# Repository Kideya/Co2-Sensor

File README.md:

Ich bin ein Pferd und weiß nicht wie man ein Readme schreibt. Man mag es mir verzeihen.
Cheers.

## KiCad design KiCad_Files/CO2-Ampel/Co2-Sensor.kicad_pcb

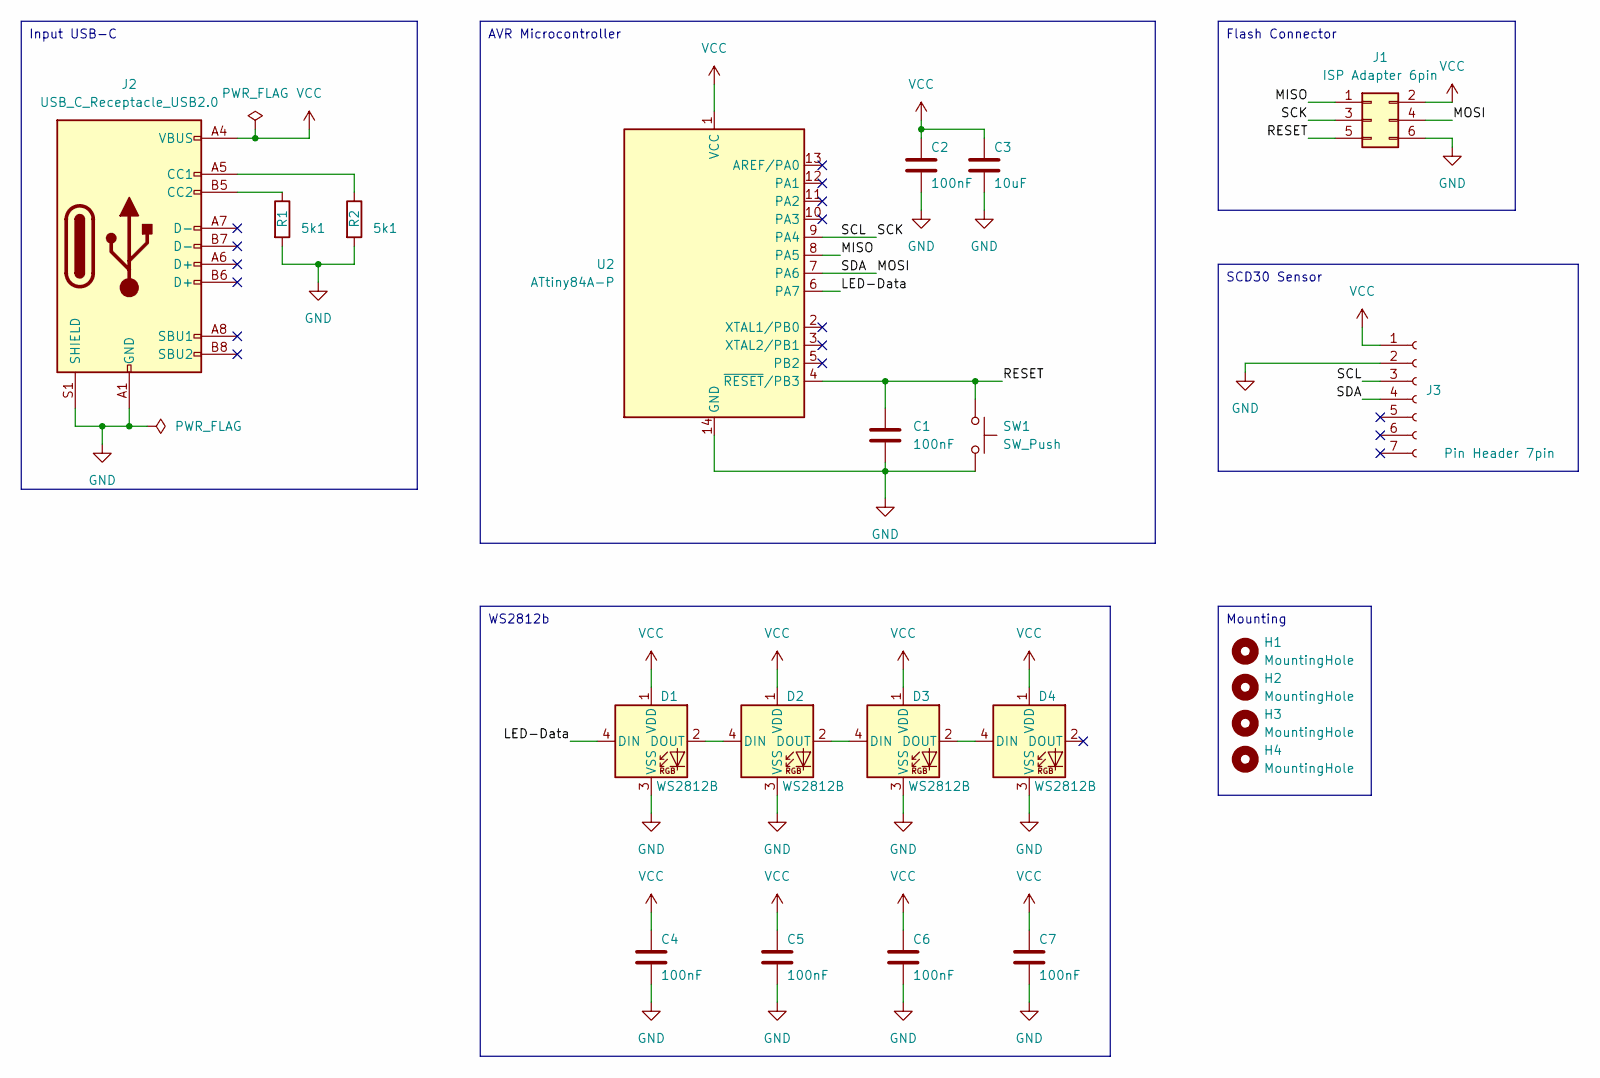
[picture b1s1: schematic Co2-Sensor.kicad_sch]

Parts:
C1, C2, C4, C5, C6, C7: 100nF; C_0603_1608Metric_Pad1.08x0.95mm_HandSolder
C3: 10uF; C_0603_1608Metric_Pad1.08x0.95mm_HandSolder
D1, D2, D3, D4: WS2812B; LED_WS2812B_PLCC4_5.0x5.0mm_P3.2mm
H1, H2, H3, H4: MountingHole; MountingHole_3.2mm_M3_ISO14580
J1: ISP Adapter 6pin; PinHeader_2x03_P2.54mm_Vertical
J2: USB_C_Receptacle_USB2.0; USB_C_Receptacle_Palconn_UTC16-G
J3: Pin Header 7pin; PinHeader_1x07_P2.54mm_Vertical
R1, R2: 5k1; R_0603_1608Metric_Pad0.98x0.95mm_HandSolder
SW1: SW_Push; SW_SPST_EVQQ2
U2: ATtiny84A-P; DIP-14_W7.62mm

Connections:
/LED-Data: D1.4 (DIN), U2.6 (PA7)
/MISO: J1.1, U2.8 (PA5)
/MOSI: J1.4, J3.4, U2.7 (PA6)
/RESET: C1.1, J1.5, SW1.1, U2.4 (~RESET/PB3)
/SCK: J1.3, J3.3, U2.9 (PA4)
GND: C1.2, C2.2, C3.2, C4.2, C5.2, C6.2, C7.2, D1.3 (VSS), D2.3 (VSS), D3.3 (VSS), D4.3 (VSS), J1.6, J2.A1 (GND), J2.A12 (GND), J2.B1 (GND), J2.B12 (GND), J2.S1 (SHIELD), J3.2, R1.2, R2.2, SW1.2, U2.14 (GND)
unnamed: D1.2 (DOUT), D2.4 (DIN)
unnamed: D2.2 (DOUT), D3.4 (DIN)
unnamed: D3.2 (DOUT), D4.4 (DIN)
unnamed: J2.A5 (CC1), R2.1
unnamed: J2.B5 (CC2), R1.1
VCC: C2.1, C3.1, C4.1, C5.1, C6.1, C7.1, D1.1 (VDD), D2.1 (VDD), D3.1 (VDD), D4.1 (VDD), J1.2, J2.A4 (VBUS), J2.A9 (VBUS), J2.B4 (VBUS), J2.B9 (VBUS), J3.1, U2.1 (VCC)

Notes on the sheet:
Input USB-C
SCD30 Sensor
Mounting
AVR Microcontroller
WS2812b
Flash Connector

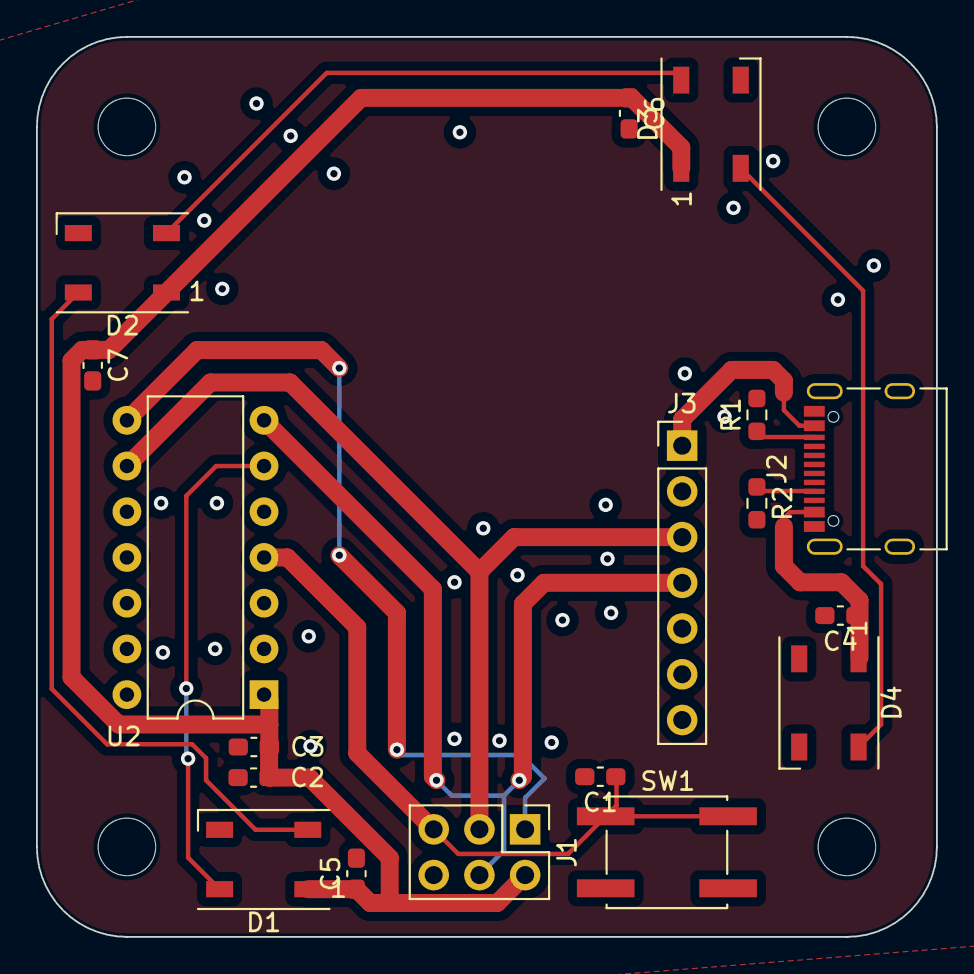
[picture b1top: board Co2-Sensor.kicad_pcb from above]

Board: 2 copper layers, 50.0 x 50.0 mm, 22 parts (0 on the bottom side), 12 nets.

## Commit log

2024-02-08 Co2 Sensor
2024-02-08 added - KiCad files
2024-02-08 - added: SDC30 Sensor Libary - added: code for sensor
2024-02-12 added code for flashing to ATtiny84
2024-09-20 Removed some Stl Files
2024-09-20 Removed uneccessary backups
